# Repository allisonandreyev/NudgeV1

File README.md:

# NudgeV1
The initial github repository for the Nudge device.

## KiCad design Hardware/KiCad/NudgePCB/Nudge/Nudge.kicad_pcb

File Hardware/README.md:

# Nudge Hardware

This directory contains the physical design files and electrical specifications for the Nudge wearable device.

## Contents

- CAD Models: 3D design files for the wearable chassis, electrode housings, and mechanical components.
- Electrical Diagrams: an early EMG test schematic.
- `KiCad/NudgeV2Rev2`: **the board in use**, Nudge v2 rev2 (schematic, netlist, PDF, firmware
  notes). XIAO ESP32-S3, one MyoWare 2.0 on J2, one DC motor with encoder on a DRV8833, USB-C
  charging and a push-button power switch. No PCB layout file was included.
- `KiCad/NudgePCB`: the 16-pad EMG strip designs, from `Nudge Fall Internship.zip`
  (firmware for these is on the `16-pad-emg-strip` branch):
  - `Nudge`: main board. J2 is now the 12-pin EMG strip header (was the MyoWare connector).
    The PCB is an unrouted placement draft.
  - `NudgeEMGStrip`: the 16-pad EMG strip. C7 replaced by a 0 Ω jumper (R2) so VCAP3 gets 1 µF.
  The git history shows each change against the original files.

## Component Specifications

Rev2 board:

- Microcontroller: Seeed XIAO ESP32-S3
- EMG: one MyoWare 2.0 muscle sensor (analog envelope output)
- Motor: one N20 DC gear motor with a single-channel hall encoder, winding a line on a spool;
  elastic cords open the hand. DRV8833 driver with about 1 A current limit, from a 9 V boost
- Power: 1S LiPo, MCP73831 USB-C charger, MAX16054 push-button on/off
- Sensors: battery voltage (force-sensor connectors are fitted but unused)
- Communication: Bluetooth Low Energy (BLE)

Pin-by-pin wiring, the strip's pad map, and known schematic issues: `Software/Nudge_Firmware/WIRING.md`.

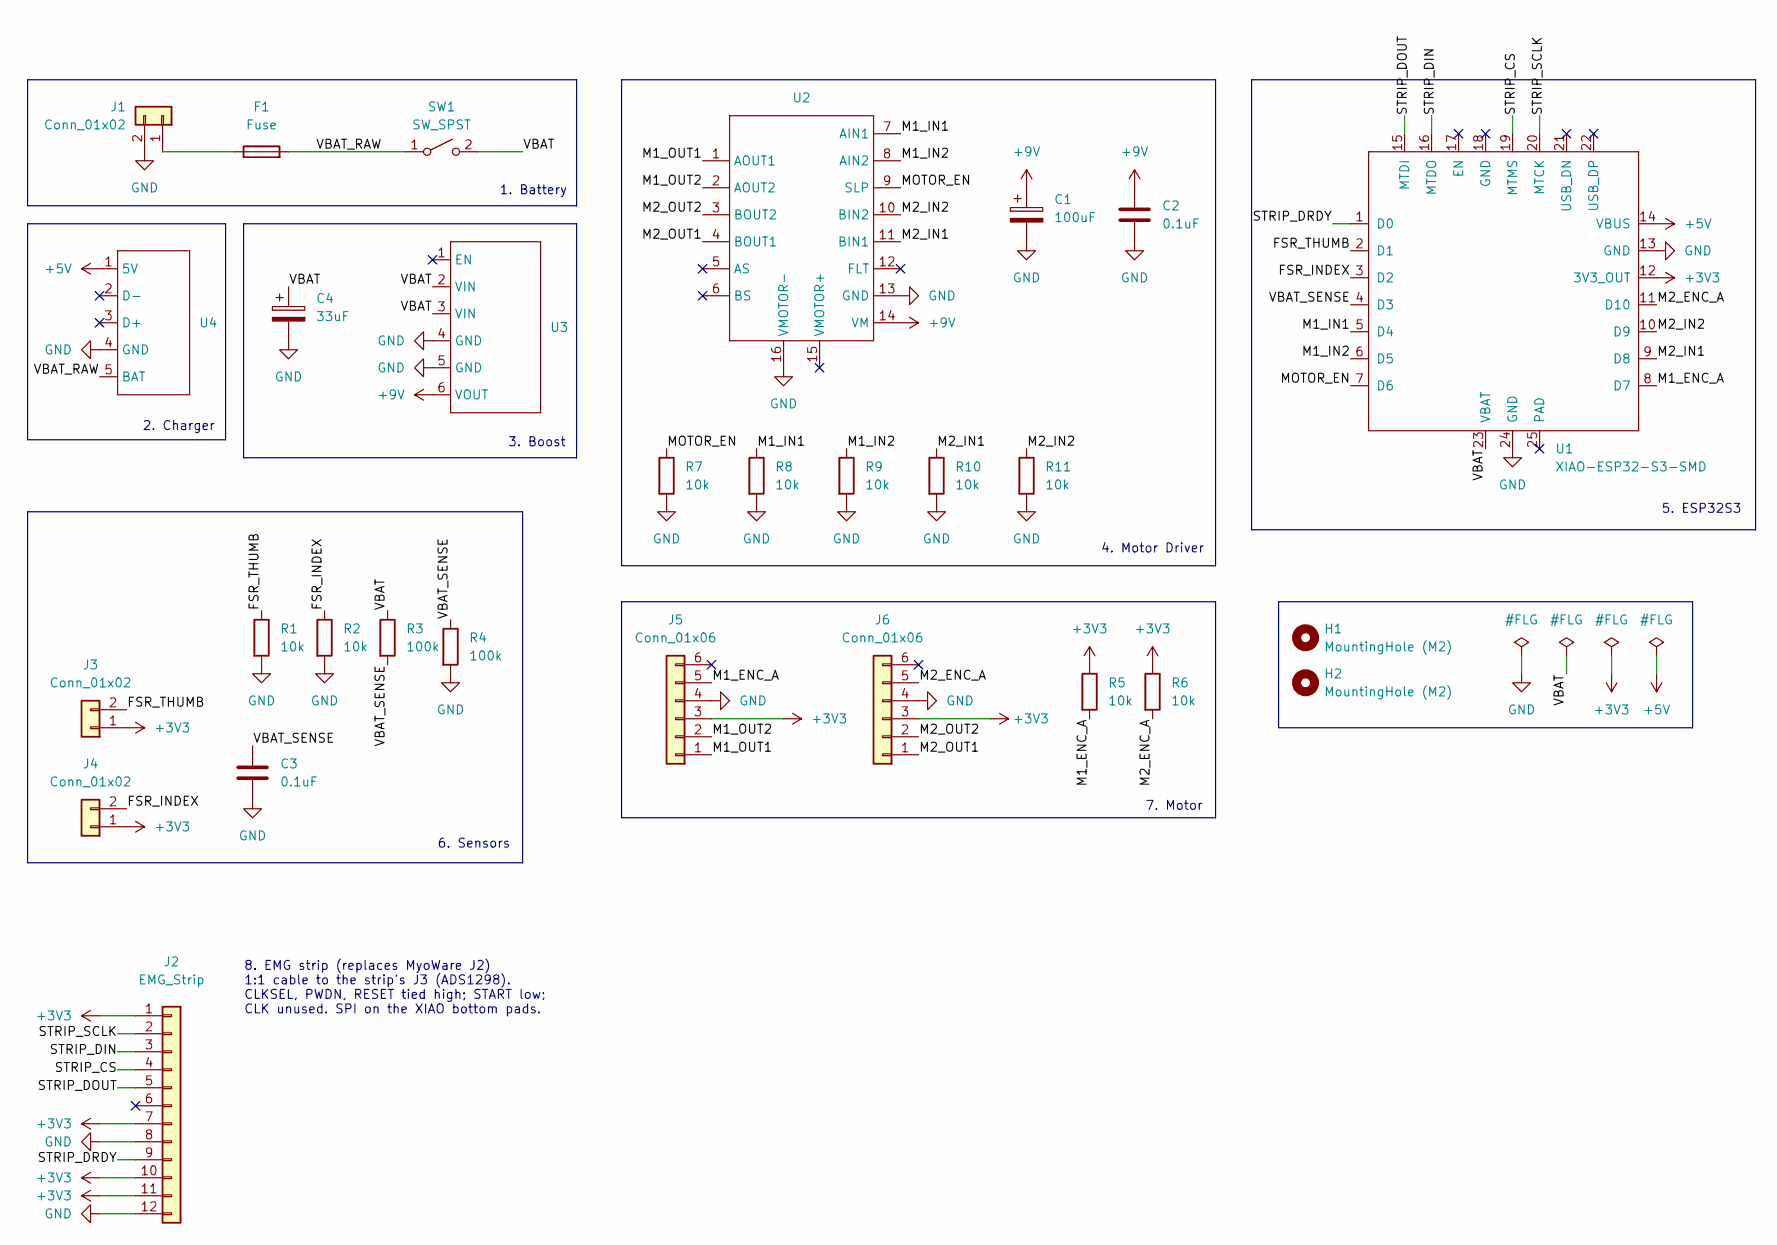
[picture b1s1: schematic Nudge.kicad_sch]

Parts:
C1: 100uF; CP_Elec_6.3x5.4
C2, C3: 0.1uF; C_0805_2012Metric_Pad1.18x1.45mm_HandSolder
C4: 33uF; CP_Elec_5x5.4
F1: Fuse; Fuse_1812_4532Metric_Pad1.30x3.40mm_HandSolder
H1, H2: MountingHole (M2); MountingHole_2.2mm_M2
J1, J3, J4: Conn_01x02; JST_PH_S2B-PH-K_1x02_P2.00mm_Horizontal
J2: EMG_Strip; PinHeader_1x12_P2.54mm_Vertical
J5, J6: Conn_01x06; JST_ZH_S6B-ZR-SM4A-TF_1x06-1MP_P1.50mm_Horizontal
R1, R2, R5, R6, R7, R8, R9, R10, R11: 10k; R_0805_2012Metric_Pad1.20x1.40mm_HandSolder
R3, R4: 100k; R_0805_2012Metric_Pad1.20x1.40mm_HandSolder
SW1: SW_SPST; PinHeader_1x02_P2.54mm_Vertical
U1: XIAO-ESP32-S3-SMD
U2: Adafruit_DRV8833
U3: PinHeader_1x06_P2.54mm_Vertical
U4: PinHeader_1x05_P2.54mm_Vertical

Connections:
+3V3: J2.1, J2.7, J2.10, J2.11, J3.1, J4.1, J5.3, J6.3, R5.1, R6.1, U1.12 (3V3_OUT)
+5V: U1.14 (VBUS), U4.1 (5V)
+9V: C1.1, C2.1, U2.14 (VM), U3.6 (VOUT)
/FSR_INDEX: J4.2, R2.1, U1.3 (D2)
/FSR_THUMB: J3.2, R1.1, U1.2 (D1)
/M1_ENC_A: J5.5, R5.2, U1.8 (D7)
/M1_IN1: R8.1, U1.5 (D4), U2.7 (AIN1)
/M1_IN2: R9.1, U1.6 (D5), U2.8 (AIN2)
/M1_OUT1: J5.1, U2.1 (AOUT1)
/M1_OUT2: J5.2, U2.2 (AOUT2)
/M2_ENC_A: J6.5, R6.2, U1.11 (D10)
/M2_IN1: R10.1, U1.9 (D8), U2.11 (BIN1)
/M2_IN2: R11.1, U1.10 (D9), U2.10 (BIN2)
/M2_OUT1: J6.1, U2.4 (BOUT1)
/M2_OUT2: J6.2, U2.3 (BOUT2)
/MOTOR_EN: R7.1, U1.7 (D6), U2.9 (SLP)
/STRIP_CS: J2.4, U1.19 (MTMS)
/STRIP_DIN: J2.3, U1.16 (MTDO)
/STRIP_DOUT: J2.5, U1.15 (MTDI)
/STRIP_DRDY: J2.9, U1.1 (D0)
/STRIP_SCLK: J2.2, U1.20 (MTCK)
/VBAT: C4.1, R3.1, SW1.2 (B), U1.23 (VBAT), U3.2 (VIN), U3.3 (VIN)
/VBAT_RAW: F1.2, SW1.1 (A), U4.5 (BAT)
/VBAT_SENSE: C3.1, R3.2, R4.1, U1.4 (D3)
GND: C1.2, C2.2, C3.2, C4.2, J1.2, J2.8, J2.12, J5.4, J6.4, R1.2, R2.2, R4.2, R7.2, R8.2, R9.2, R10.2, R11.2, U1.13 (GND), U1.24 (GND), U2.13 (GND), U2.16 (VMOTOR-), U3.4 (GND), U3.5 (GND), U4.4 (GND)
unnamed: F1.1, J1.1

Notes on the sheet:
4. Motor Driver
5. ESP32S3
3. Boost
7. Motor
2. Charger
1. Battery
6. Sensors
8. EMG strip (replaces MyoWare J2) 1:1 cable to the strip's J3 (ADS1298). CLKSEL, PWDN, RESET tied high; START low; CLK unused. SPI on the XIAO bottom pads.

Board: 2 copper layers, 29 parts (0 on the bottom side), 26 nets, no tracks yet.

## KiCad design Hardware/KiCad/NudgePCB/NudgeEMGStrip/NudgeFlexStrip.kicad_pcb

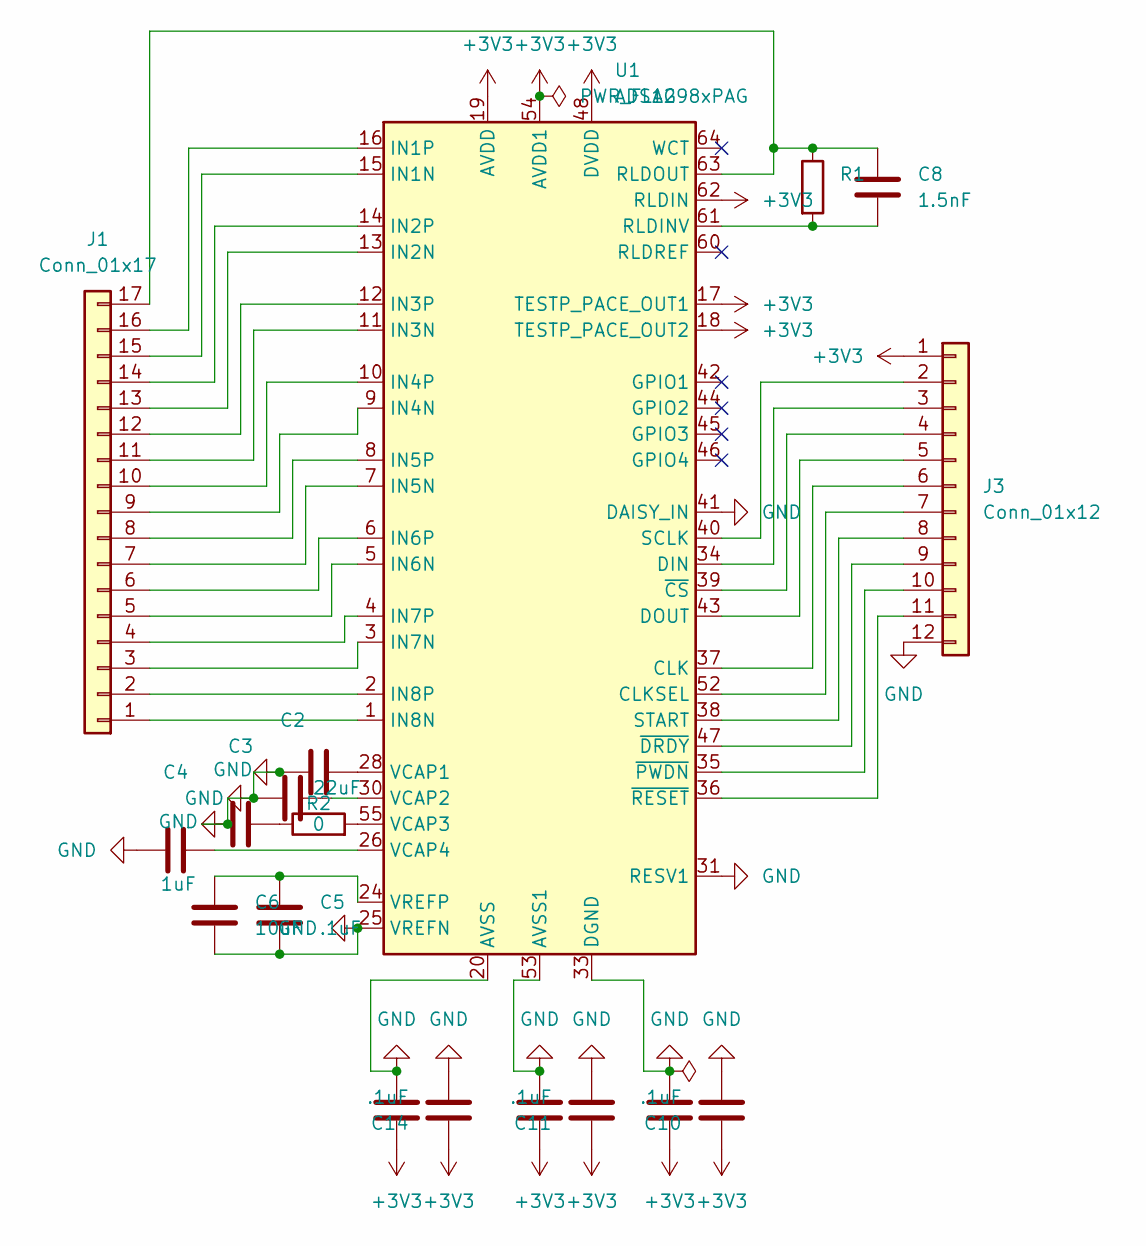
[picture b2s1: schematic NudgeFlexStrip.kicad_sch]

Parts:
C1: 22uF; C_1206_3216Metric
C2, C3, C4, C12, C13, C15: 1uF; C_0603_1608Metric
C5, C10, C11, C14: .1uF; C_0603_1608Metric
C6: 10uF; C_0603_1608Metric
C8: 1.5nF; C_0603_1608Metric
J1: Conn_01x17; Electrode_Pad
J3: Conn_01x12; PinHeader_1x12_P2.54mm_Vertical
R1: 1MQ; R_0603_1608Metric
R2: 0; R_0603_1608Metric
U1: ADS1298xPAG; TQFP-64_10x10mm_P0.5mm

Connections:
+3V3: C10.2, C11.2, C12.2, C13.2, C14.2, C15.2, J3.1, U1.17 (TESTP_PACE_OUT1), U1.18 (TESTP_PACE_OUT2), U1.19 (AVDD), U1.21 (AVDD), U1.22 (AVDD), U1.48 (DVDD), U1.50 (DVDD), U1.54 (AVDD1), U1.56 (AVDD), U1.59 (AVDD), U1.62 (RLDIN)
GND: C1.1, C2.1, C3.1, C4.1, C5.2, C6.2, C10.1, C11.1, C12.1, C13.1, C14.1, C15.1, J3.12, U1.20 (AVSS), U1.23 (AVSS), U1.25 (VREFN), U1.31 (RESV1), U1.32 (AVSS), U1.33 (DGND), U1.41 (DAISY_IN), U1.49 (DGND), U1.51 (DGND), U1.53 (AVSS1), U1.57 (AVSS), U1.58 (AVSS)
unnamed: C3.2, R2.1
unnamed: J1.1, U1.1 (IN8N)
unnamed: J1.2, U1.2 (IN8P)
unnamed: J1.3, U1.3 (IN7N)
unnamed: J1.4, U1.4 (IN7P)
unnamed: J1.5, U1.5 (IN6N)
unnamed: J1.6, U1.6 (IN6P)
unnamed: J1.7, U1.7 (IN5N)
unnamed: J1.8, U1.8 (IN5P)
unnamed: J1.9, U1.9 (IN4N)
unnamed: J1.10, U1.10 (IN4P)
unnamed: J1.11, U1.11 (IN3N)
unnamed: J1.12, U1.12 (IN3P)
unnamed: J1.13, U1.13 (IN2N)
unnamed: J1.14, U1.14 (IN2P)
unnamed: J1.15, U1.15 (IN1N)
unnamed: J1.16, U1.16 (IN1P)
unnamed: C8.1, J1.17, R1.1, U1.63 (RLDOUT)
unnamed: J3.2, U1.40 (SCLK)
unnamed: J3.3, U1.34 (DIN)
unnamed: J3.4, U1.39 (~CS)
unnamed: J3.5, U1.43 (DOUT)
unnamed: J3.6, U1.37 (CLK)
unnamed: J3.7, U1.52 (CLKSEL)
unnamed: J3.8, U1.38 (START)
unnamed: J3.9, U1.47 (~DRDY)
unnamed: J3.10, U1.35 (~PWDN)
unnamed: J3.11, U1.36 (~RESET)
unnamed: C8.2, R1.2, U1.61 (RLDINV)
unnamed: C1.2, U1.28 (VCAP1)
unnamed: C2.2, U1.30 (VCAP2)
unnamed: R2.2, U1.55 (VCAP3)
unnamed: C4.2, U1.26 (VCAP4)
unnamed: C5.1, C6.1, U1.24 (VREFP)

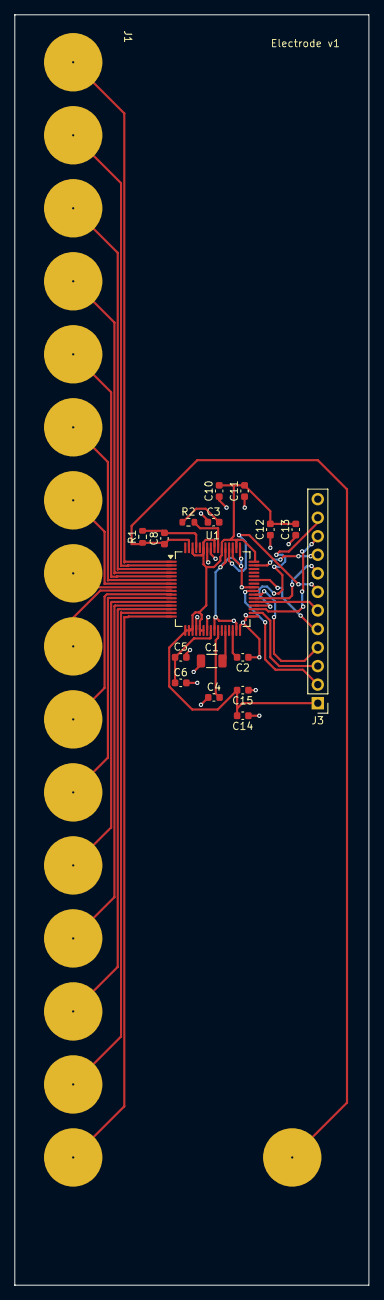
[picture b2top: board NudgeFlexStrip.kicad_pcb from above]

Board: 2 copper layers, 48.5 x 174.0 mm, 18 parts (0 on the bottom side), 36 nets.

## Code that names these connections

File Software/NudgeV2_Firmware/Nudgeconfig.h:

#pragma once
#include <Arduino.h>

// =====================================================================
//  Nudge N20 Firmware - configuration
//  Board: Seeed XIAO ESP32-S3 (V2 schematic pin map)
//  Every pin lives here. Set an optional pin to -1 to disable it.
// =====================================================================

// ---------------- Sensors ----------------
constexpr int PIN_EMG_FLEXOR   = D0;   // MyoWare ENV output, grip muscle
constexpr int PIN_EMG_EXTENSOR = -1;   // optional 2nd MyoWare, open muscle (no free pin on V2 yet)
constexpr int PIN_FSR_THUMB    = D1;   // FSR with 10k pull-down
constexpr int PIN_FSR_INDEX    = D2;   // FSR with 10k pull-down
constexpr int PIN_VBAT_SENSE   = D3;   // 100k/100k battery divider
constexpr float VBAT_DIVIDER   = 2.0f; // battery mV = pin mV * this

// ---------------- DRV8833 motor driver ----------------
constexpr int PIN_MOTOR_EN = D6;       // DRV8833 SLP (HIGH = awake)

// Motor 1 = four fingers
constexpr int PIN_M1_IN1   = D4;
constexpr int PIN_M1_IN2   = D5;
constexpr int PIN_M1_ENC_A = D7;

// Motor 2 = thumb
constexpr int PIN_M2_IN1   = D8;
constexpr int PIN_M2_IN2   = D9;
constexpr int PIN_M2_ENC_A = D10;

// Optional physical stop button to GND (uses internal pull-up)
constexpr int PIN_ESTOP_BUTTON = -1;

// ---------------- Motor calibration (MEASURE THESE) ----------------
// Flip if a motor runs the wrong way on "grasp" (closing must count UP).
constexpr bool M1_REVERSED = false;
constexpr bool M2_REVERSED = false;

// Encoder counts from fully open (0) to fully closed. Find them with the
// "jog" and "status" commands, then enter them here.
constexpr long M1_CLOSED_COUNTS = 400;
constexpr long M2_CLOSED_COUNTS = 300;

constexpr uint8_t  DEFAULT_SPEED_PCT  = 60;    // normal drive strength
constexpr uint8_t  MIN_SPEED_PCT      = 30;    // floor when slowing near target
constexpr long     SLOWDOWN_COUNTS    = 40;    // start slowing this close to target
constexpr long     POSITION_TOLERANCE = 5;     // "arrived" window in counts
constexpr uint32_t PWM_FREQ_HZ        = 20000; // above hearing range
constexpr uint8_t  PWM_RES_BITS       = 10;

// ---------------- Safety ----------------
constexpr uint32_t STALL_TIME_MS   = 200;  // no encoder movement this long = stalled
constexpr uint32_t STALL_GRACE_MS  = 150;  // ignore stalls during spin-up
constexpr uint32_t MOVE_TIMEOUT_MS = 4000; // hard limit on any single move
constexpr uint32_t THUMB_DELAY_MS  = 150;  // thumb starts this long after fingers
constexpr int      FSR_STOP_MV     = 2000; // grip force limit (FSR pin millivolts)
constexpr int      VBAT_MIN_MV     = 3400; // refuse to grasp below this

// ---------------- Timing ----------------
constexpr uint32_t SENSOR_RATE_HZ  = 200;  // MUST match the Edge Impulse training rate
constexpr uint32_t CONTROL_RATE_HZ = 100;  // motor control loop
constexpr uint32_t BLE_RATE_HZ     = 25;   // packets to the phone app

// ---------------- AI (Edge Impulse) ----------------
// 0 = build without a model (manual commands only)
// 1 = include your Edge Impulse library (edit the #include in the .ino)
#define USE_EDGE_IMPULSE 0

constexpr float    AI_CONFIDENCE    = 0.80f; // ignore predictions below this
constexpr int      AI_STABILITY     = 3;     // same label N times in a row to act
constexpr uint32_t AI_STRIDE_MS     = 50;    // run the model this often
// With a single EMG sensor the model can only tell GRIP from REST, so REST
// must open the hand ("hold while squeezing"). With a flexor + extensor pair
// and an OPEN label, set this to false so the hand stays closed until OPEN.
constexpr bool     AI_REST_RELEASES = true;

constexpr int NUM_EMG = (PIN_EMG_EXTENSOR >= 0) ? 2 : 1;

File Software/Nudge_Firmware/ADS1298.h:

#pragma once
#include <Arduino.h>
#include "ADS1298Frame.h"
#include "BoardConfig.h"

/**
 * Driver for the TI ADS1298 on the 16-pad EMG strip (8 differential channels).
 * Wiring, pad map and bring-up steps: WIRING.md.
 *
 * After Begin(), a background task reads every conversion on DRDY, filters it and
 * produces 50 Hz envelope frames (microvolts per channel) for the gesture model.
 */
namespace ADS1298
{
    constexpr int CHANNELS = ADS1298Frame::CHANNELS;

    // --- Pins: set in BoardConfig.h (-1 = tied on the strip's header instead of driven) ---
    constexpr int PIN_SCLK = Board::PIN_STRIP_SCLK;
    constexpr int PIN_DIN = Board::PIN_STRIP_DIN;
    constexpr int PIN_CS = Board::PIN_STRIP_CS;
    constexpr int PIN_DOUT = Board::PIN_STRIP_DOUT;
    constexpr int PIN_START = Board::PIN_STRIP_START;
    constexpr int PIN_DRDY = Board::PIN_STRIP_DRDY;
    constexpr int PIN_PWDN = Board::PIN_STRIP_PWDN;
    constexpr int PIN_RESET = Board::PIN_STRIP_RESET;
    constexpr int PIN_CLKSEL = Board::PIN_STRIP_CLKSEL;

    // --- Signal settings --------------------------------------------------------------
    constexpr int SAMPLE_RATE = 250;  // 250 (low-power mode) or 500 (high-resolution mode)
    constexpr int GAIN = 6;           // PGA gain: 1, 2, 3, 4, 6, 8 or 12. 6 is the chip default.
    constexpr float VREF = 2.4f;      // internal reference; 4 V needs a 5 V supply
    constexpr float MAINS_HZ = 60;    // 50 in Europe, 0 to turn the notch off
    constexpr uint32_t SPI_HZ = 4000000;

    /** What the channel inputs are connected to. Everything but Electrodes is for bring-up. */
    enum class InputMode : uint8_t
    {
        Electrodes = 0x0,   // normal
        Shorted = 0x1,      // inputs shorted together: shows the noise floor, should be near 0 uV
        Supply = 0x3,       // measures the supply (MVDD): a large, steady value
        Temperature = 0x4,  // on-chip temperature sensor: steady, about 145 mV at 25 C
        TestSignal = 0x5    // internal ~1 Hz square wave (see WIRING.md caveat)
    };

    struct Stats
    {
        uint32_t frames;     // conversions read
        uint32_t badFrames;  // status word didn't start with 1100: SPI or wiring problem
        uint32_t dropped;    // envelope frames lost because nothing consumed them
        float rateHz;        // measured conversions per second over the last report
        float peakToPeakUv[CHANNELS];  // raw signal swing over the last report
        float rmsUv[CHANNELS];         // filtered signal level over the last report
    };

    /** Powers up, checks the chip ID, configures and starts streaming. Prints progress to Serial. */
    bool Begin();

    /** Device ID register; 0x92 for ADS1298, 0xD2 for ADS1298R. */
    uint8_t DeviceId();

    bool SetInputMode(InputMode mode);
    InputMode CurrentMode();

    /** Waits up to [timeoutMs] for the next 50 Hz envelope frame (microvolts per channel). */
    bool NextEnvelope(float out[CHANNELS], uint32_t timeoutMs);

    /** Statistics since the previous call. */
    Stats TakeStats();

    /**
     * Handles "ads ..." text commands (from BLE or Serial). Returns false if [cmd] isn't one.
     *   ads mode electrodes|shorted|supply|temp|test
     *   ads diag on|off     print signal stats to Serial every second
     */
    bool HandleCommand(const String& cmd);

    /** Prints stats to Serial once a second if diagnostics are on. Call from loop(). */
    void PrintDiagnostics();
}
